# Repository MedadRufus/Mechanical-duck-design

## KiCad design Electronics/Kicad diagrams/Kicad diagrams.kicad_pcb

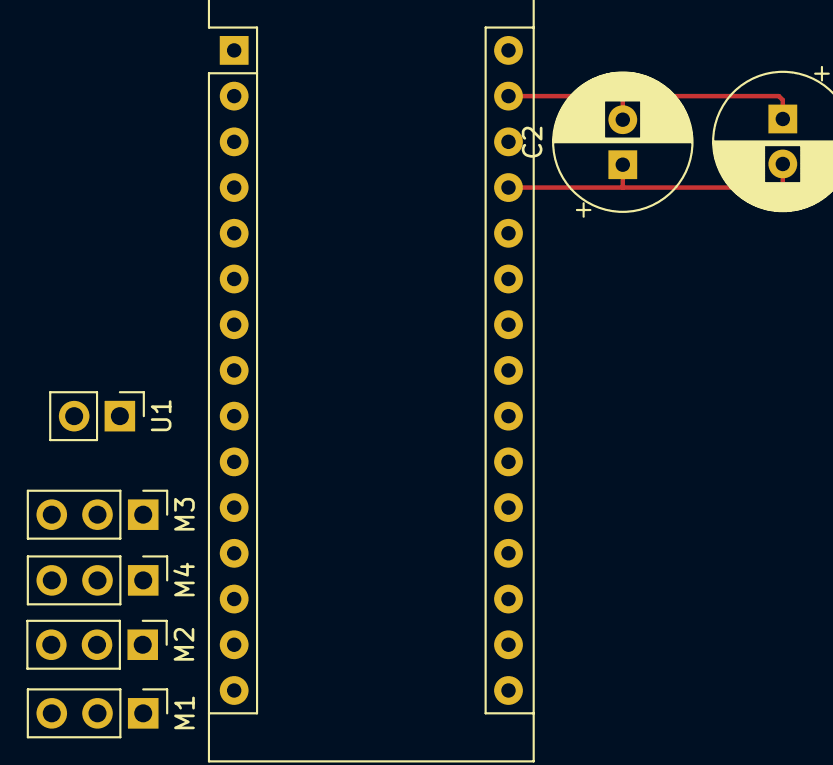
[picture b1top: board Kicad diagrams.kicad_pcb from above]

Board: 2 copper layers, 8 parts (0 on the bottom side), 7 nets.

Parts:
A1: Arduino_Nano_v3.x; Arduino_Nano
C1: C100u; CP_Radial_D7.5mm_P2.50mm
C2: C470u; CP_Radial_D7.5mm_P2.50mm
M1, M2, M3, M4: Motor_Servo; PinHeader_1x03_P2.54mm_Vertical
U1: TR6_receiver; PinHeader_1x02_P2.54mm_Vertical

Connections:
GND: A1.4, A1.29, C1.1, C2.2, M1.3, M2.3, M3.3, M4.3, U1.2
unnamed: A1.12, M3.1
unnamed: A1.13, M4.1
unnamed: A1.14, M2.1
unnamed: A1.15, M1.1
unnamed: A1.27, C1.2, C2.1
VCC: A1.30, M1.2, M2.2, M3.2, M4.2, U1.1

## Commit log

2019-01-18 Added the code to run the left and right servos
2019-02-14 added a 4 bar linkage feet
2019-02-16 more progress in designing the arm mechnism
2019-02-19 made more improvements to the 4 bar linkage design
2019-02-19 more changes to the linkage model
2019-02-21 added a new full duck model
2019-02-22 Designed a second design
2019-02-22 added a 3rd duck design with stacked servos
2019-02-23 compartmentalised the Software
2019-02-23 completed the drivers for the servos and the radio
2019-02-23 Added more helper functions to the software to drive the servos. Also experimenting with a 5 bar linkage
2019-02-23 more duck code helpers
2019-02-25 Implemented the state machine in the Code
2019-02-26 confirmed the design of the Legs of the duck
2019-02-28 made many many mechanical designs
2019-02-28 making final lasercut enclosure
2019-03-01 Finalised the design of the duck structure, updated the driver code for servos
2019-03-01 backtrack
2019-03-04 getting ready for actual presentation
2019-03-05 updated the schematic with the decoupling capacitor
2019-04-29 report submission day
2019-04-29 changed title of the final code directory
2019-04-29 submitted!!
2019-05-02 cleaned up the software code to include some comments.
